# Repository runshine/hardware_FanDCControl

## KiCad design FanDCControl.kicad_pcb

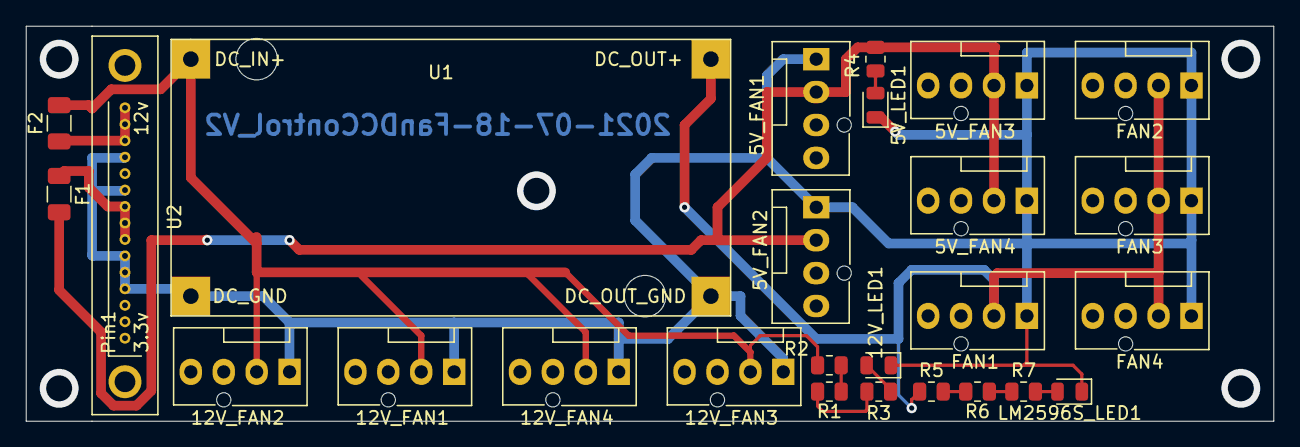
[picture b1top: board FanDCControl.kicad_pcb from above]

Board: 2 copper layers, 96.3 x 30.5 mm, 26 parts (0 on the bottom side), 13 nets.

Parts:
5V_FAN1, 5V_FAN2, 5V_FAN3, 5V_FAN4, 12V_FAN1, 12V_FAN2, 12V_FAN3, 12V_FAN4: Fan_Tacho_PWM; FanPinHeader_1x04_P2.54mm_Vertical
5V_LED1: GREEN_LED; LED_0805_2012Metric
12V_LED1: RED_LED; LED_0805_2012Metric
F1: 5V_Polyfuse; Fuse_1206_3216Metric
F2: 12V_Polyfuse; Fuse_1206_3216Metric
FAN1, FAN2, FAN3, FAN4: Fan_Tacho_PWM; FanPinHeader_1x04_P2.54mm_Vertical
LM2596S_LED1: BLUE_LED; LED_0805_2012Metric
R1, R2: 1000R; R_0805_2012Metric
R3: 1R; R_0805_2012Metric
R4: 680R; R_0805_2012Metric
R5, R6, R7: 150R; R_0805_2012Metric
U1: LM2596S_DC_MODEL_4
U2: SATA_POWER_15; SATA_POWER_DIP_15

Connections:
+5V: 5V_FAN1.2, 5V_FAN2.2, 5V_FAN3.2, 5V_FAN4.2, F1.2, R4.2
+8V: FAN1.2, FAN2.2, FAN3.2, FAN4.2, R5.1, U1.3
+12V: 12V_FAN1.2, 12V_FAN2.2, 12V_FAN3.2, 12V_FAN4.2, F2.2, R1.2, U1.1
GND: 5V_FAN1.1, 5V_FAN2.1, 5V_FAN3.1, 5V_FAN4.1, 5V_LED1.1, 12V_FAN1.1, 12V_FAN2.1, 12V_FAN3.1, 12V_FAN4.1, 12V_LED1.1, FAN1.1, FAN2.1, FAN3.1, FAN4.1, LM2596S_LED1.1, U1.2, U1.4, U2.4, U2.5, U2.6, U2.10, U2.12
unnamed: 5V_LED1.2, R4.1
unnamed: 12V_LED1.2, R3.1
unnamed: F1.1, U2.7, U2.8, U2.9
unnamed: F2.1, U2.13, U2.14, U2.15
unnamed: LM2596S_LED1.2, R7.2
unnamed: R1.1, R2.2
unnamed: R2.1, R3.2
unnamed: R5.2, R6.1
unnamed: R6.2, R7.1
